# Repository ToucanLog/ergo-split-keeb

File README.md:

# ergo-split-keeb
rp2040 based split keyboard with trrs and usb-c (2.0). Using an ergodox-esque layout, but I wanted even more keys...

NOTE: The firmware is for use with QMK (https://github.com/qmk/qmk_firmware), however this keyboard does not have an official commit yet. Thus, simply copy this keyboard's firmware into a new sub-folder in the "keyboards" folder and flash from there. See the QMK CLI docs for flashing the keyboard for extra help. Please note that this firmware is exceptionally early stage, and while completely functional, is relatively bare-bones. 

`qmk flash -kb "/ENTER PATH HERE" -km default -bl uf2-split-left`

`qmk flash -kb "/ENTER PATH HERE" -km default -bl uf2-split-right`

See Schematic for 1 PCB (Left)

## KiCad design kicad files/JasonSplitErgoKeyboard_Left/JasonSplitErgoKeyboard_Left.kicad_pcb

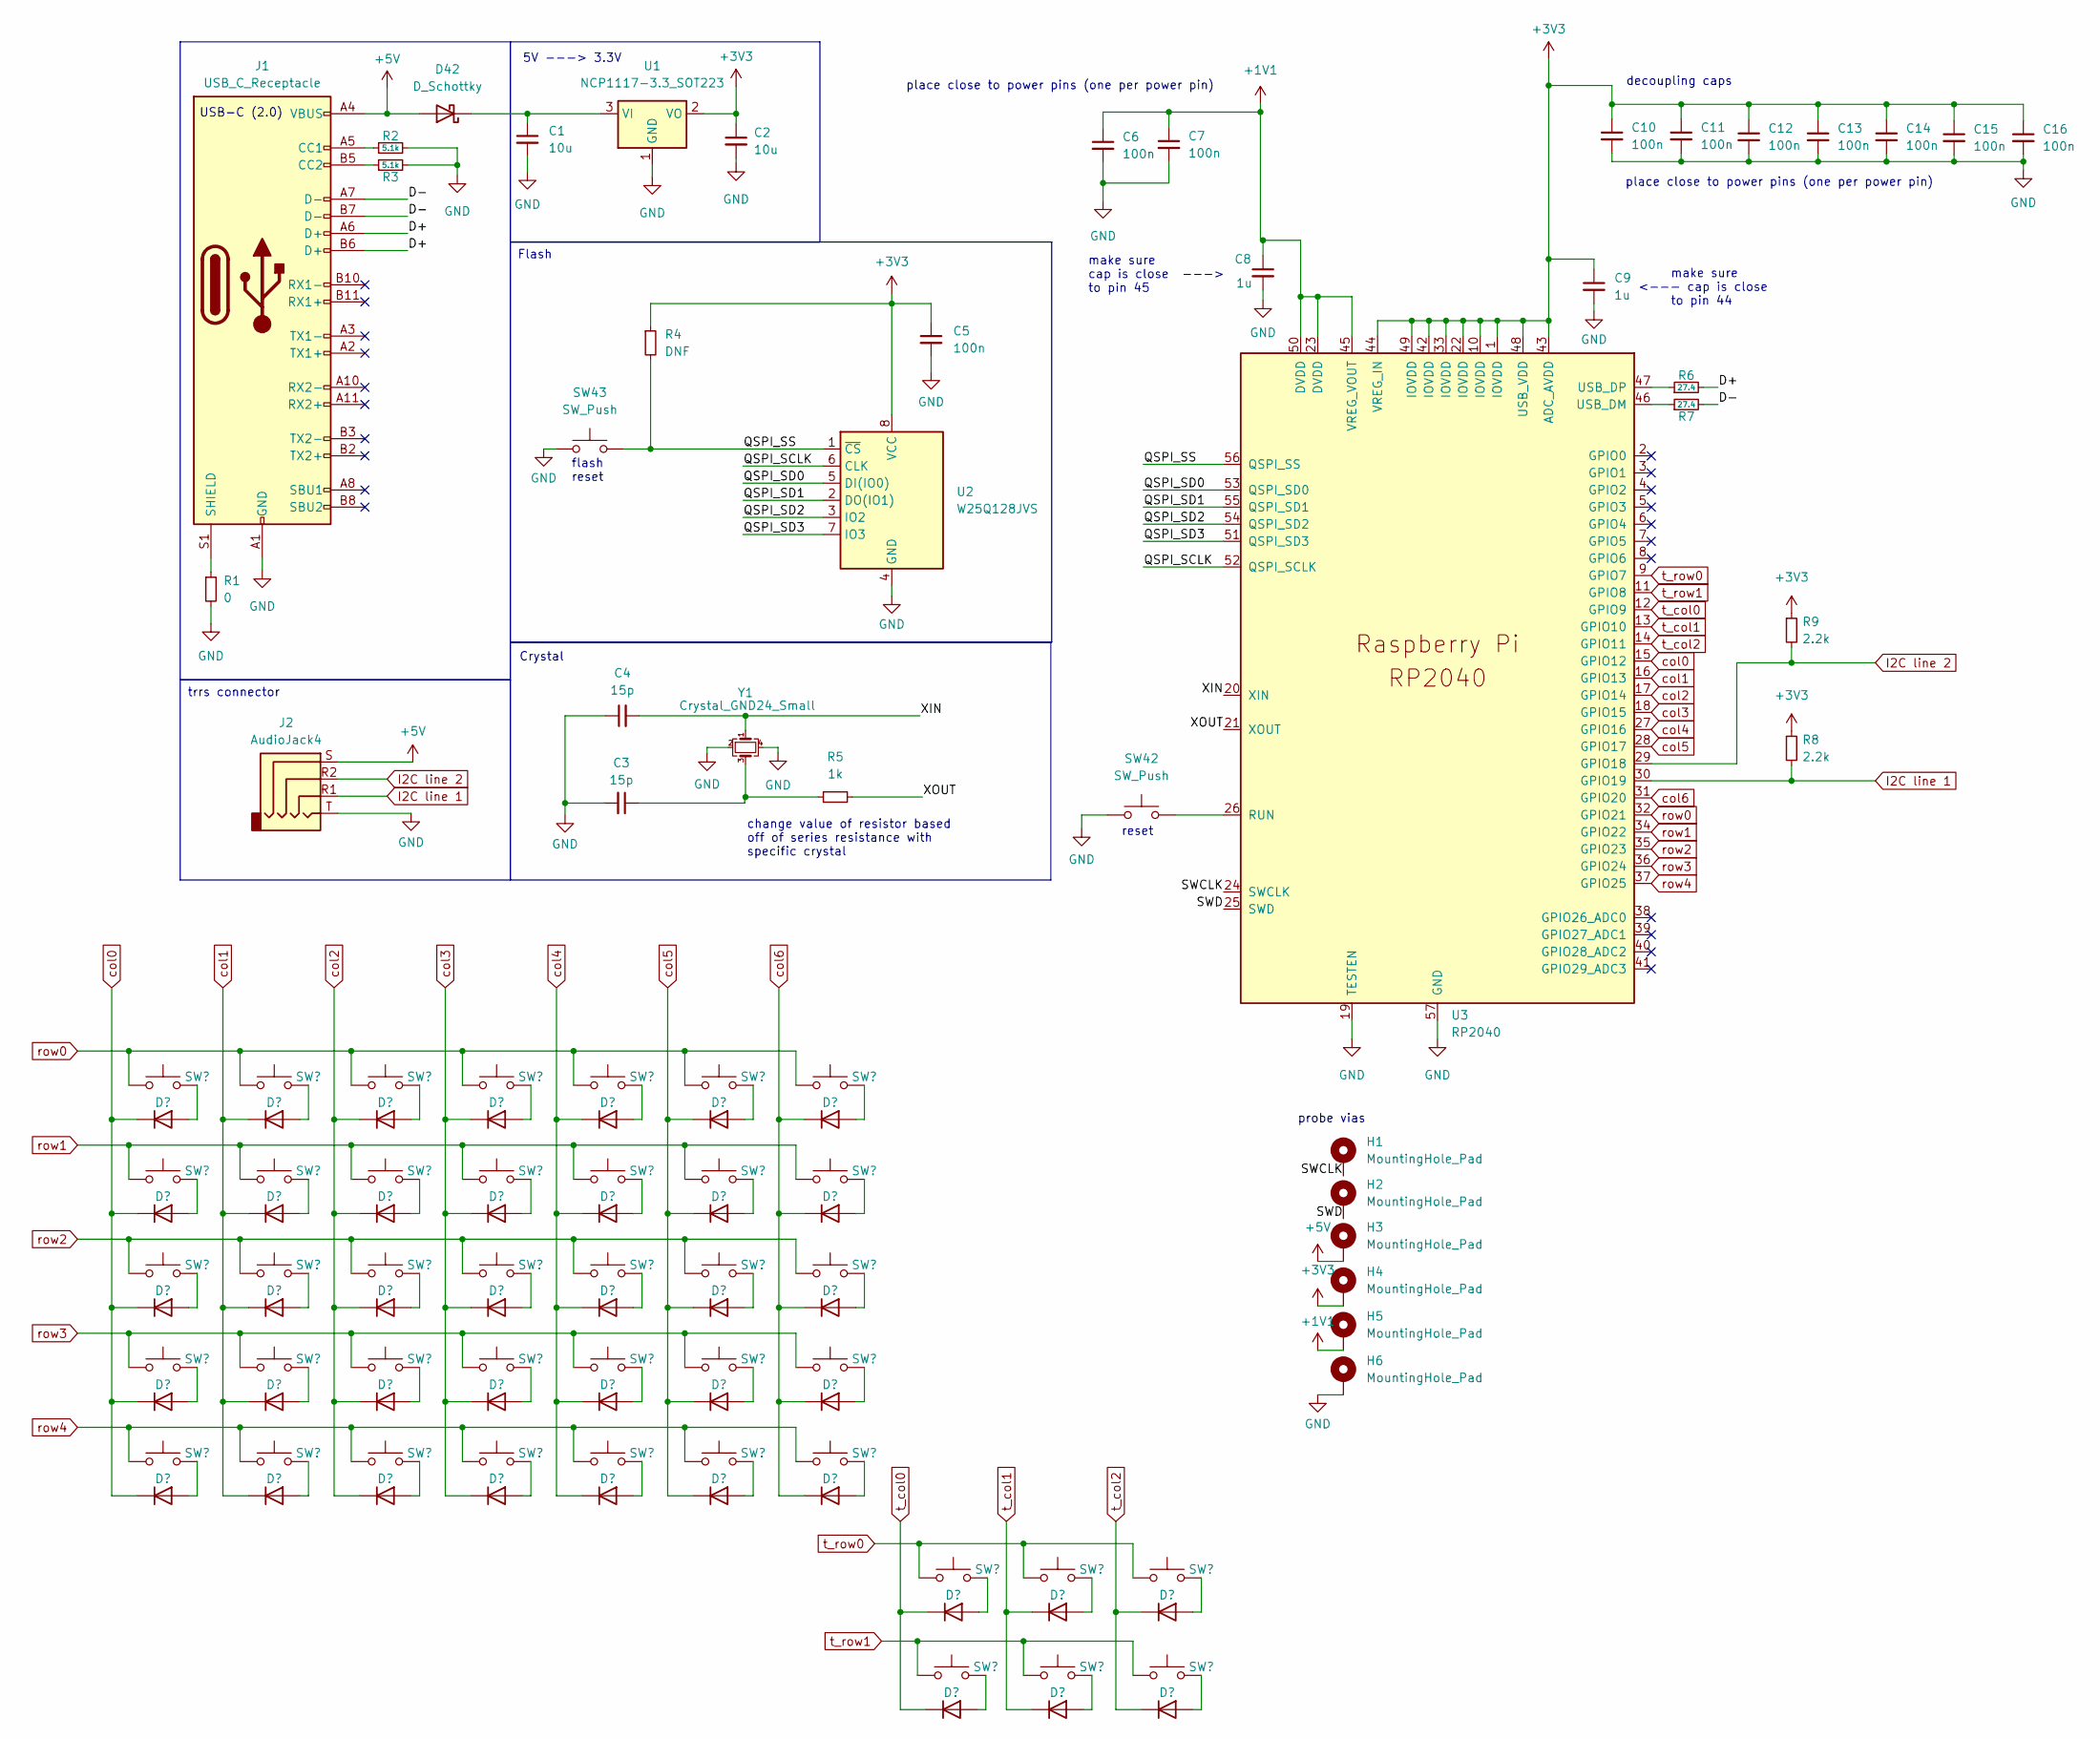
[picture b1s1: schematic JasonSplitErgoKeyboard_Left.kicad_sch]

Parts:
C1, C2: 10u; C_0603_1608Metric
C3, C4: 15p; C_0603_1608Metric
C5, C6, C7, C10, C11, C12, C13, C14, C15, C16: 100n; C_0603_1608Metric
C8, C9: 1u; C_0603_1608Metric
D1, D2, D3, D4, D5, D6, D7, D8, D9, D10, D11, D12, D13, D14, D15, D16, D17, D18, D19, D20, D21, D22, D23, D24, D25, D26, D27, D28, D29, D30, D31, D32, D33, D34, D35, D36, D37, D38, D39, D40, D41: D; D_SOD-323
D42: D_Schottky; D_SOD-323
H1, H2, H3, H4, H5, H6: MountingHole_Pad; MountingHole_2.2mm_M2_DIN965_Pad
J1: USB_C_Receptacle; USB_C_Receptacle_G-Switch_GT-USB-7010ASV
J2: AudioJack4; Jack_3.5mm_PJ320D_Horizontal
R1: 0; R_0603_1608Metric
R2, R3: 5.1k; R_0603_1608Metric
R4: DNF; R_0603_1608Metric
R5: 1k; R_0603_1608Metric
R6, R7: 27.4; R_0603_1608Metric
R8, R9: 2.2k; R_0603_1608Metric
SW1, SW2, SW3, SW4, SW7, SW8, SW9, SW10, SW11, SW12, SW13, SW14, SW15, SW16, SW17, SW18, SW19, SW20, SW21, SW22, SW23, SW24, SW25, SW26, SW27, SW28, SW29, SW30, SW31, SW32, SW33, SW34, SW35, SW36, SW41: SW_Push; SW_Cherry_MX_1.00u_PCB
SW5, SW6: SW_Push; SW_Cherry_MX_2.00u_PCB
SW37, SW38, SW39, SW40: SW_Push; SW_Cherry_MX_1.50u_PCB
SW42, SW43: SW_Push; 3.9×2.9mm Compact Type
U1: NCP1117-3.3_SOT223; SOT-223-3_TabPin2
U2: W25Q128JVS; SOIC-8_5.23x5.23mm_P1.27mm
U3: RP2040; QFN-56-1EP_7x7mm_P0.4mm_EP4x4mm
Y1: Crystal_GND24_Small; Crystal_SMD_3225-4Pin_3.2x2.5mm

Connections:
+1V1: C6.1, C7.1, C8.1, H5.1, U3.23 (DVDD), U3.45 (VREG_VOUT), U3.50 (DVDD)
+3V3: C2.1, C5.1, C9.1, C10.1, C11.1, C12.1, C13.1, C14.1, C15.1, C16.1, H4.1, R4.1, R8.1, R9.1, U1.2 (VO), U2.8 (VCC), U3.1 (IOVDD), U3.10 (IOVDD), U3.22 (IOVDD), U3.33 (IOVDD), U3.42 (IOVDD), U3.43 (ADC_AVDD), U3.44 (VREG_IN), U3.48 (USB_VDD), U3.49 (IOVDD)
+5V: D42.2 (A), H3.1, J1.A4 (VBUS), J1.A9 (VBUS), J1.B4 (VBUS), J1.B9 (VBUS), J2.S
/D+: J1.A6 (D+), J1.B6 (D+), R6.2
/D-: J1.A7 (D-), J1.B7 (D-), R7.2
/QSPI_SCLK: U2.6 (CLK), U3.52 (QSPI_SCLK)
/QSPI_SD0: U2.5 (DI(IO0)), U3.53 (QSPI_SD0)
/QSPI_SD1: U2.2 (DO(IO1)), U3.55 (QSPI_SD1)
/QSPI_SD2: U2.3 (IO2), U3.54 (QSPI_SD2)
/QSPI_SD3: U2.7 (IO3), U3.51 (QSPI_SD3)
/QSPI_SS: R4.2, SW43.2, U2.1 (~CS), U3.56 (QSPI_SS)
/SWCLK: H1.1, U3.24 (SWCLK)
/SWD: H2.1, U3.25 (SWD)
/XIN: C4.2, U3.20 (XIN), Y1.1
/XOUT: R5.2, U3.21 (XOUT)
GND: C1.2, C2.2, C3.2, C4.1, C5.2, C6.2, C7.2, C8.2, C9.2, C10.2, C11.2, C12.2, C13.2, C14.2, C15.2, C16.2, H6.1, J1.A1 (GND), J1.A12 (GND), J1.B1 (GND), J1.B12 (GND), J2.T, R1.2, R2.2, R3.2, SW42.1, SW43.1, U1.1 (GND), U2.4 (GND), U3.19 (TESTEN), U3.57 (GND), Y1.2, Y1.4
I2C line 1: J2.R1, R8.2, U3.30 (GPIO19)
I2C line 2: J2.R2, R9.2, U3.29 (GPIO18)
unnamed: C3.1, R5.1, Y1.3
unnamed: D1.2 (A), SW1.2
unnamed: D2.2 (A), SW2.2
unnamed: D3.2 (A), SW3.2
unnamed: D4.2 (A), SW4.2
unnamed: D5.2 (A), SW5.2
unnamed: D6.2 (A), SW6.2
unnamed: D7.2 (A), SW7.2
unnamed: D8.2 (A), SW8.2
unnamed: D9.2 (A), SW9.2
unnamed: D10.2 (A), SW10.2
unnamed: D11.2 (A), SW11.2
unnamed: D12.2 (A), SW12.2
unnamed: D13.2 (A), SW13.2
unnamed: D14.2 (A), SW14.2
unnamed: D15.2 (A), SW15.2
unnamed: D16.2 (A), SW16.2
unnamed: D17.2 (A), SW17.2
unnamed: D18.2 (A), SW18.2
unnamed: D19.2 (A), SW19.2
unnamed: D20.2 (A), SW20.2
unnamed: D21.2 (A), SW21.2
unnamed: D22.2 (A), SW22.2
unnamed: D23.2 (A), SW23.2
unnamed: D24.2 (A), SW24.2
unnamed: D25.2 (A), SW25.2
unnamed: D26.2 (A), SW26.2
unnamed: D27.2 (A), SW27.2
unnamed: D28.2 (A), SW28.2
unnamed: D29.2 (A), SW29.2
unnamed: D30.2 (A), SW30.2
unnamed: D31.2 (A), SW31.2
unnamed: D32.2 (A), SW32.2
unnamed: D33.2 (A), SW33.2
unnamed: D34.2 (A), SW34.2
unnamed: D35.2 (A), SW35.2
unnamed: D36.2 (A), SW36.2
unnamed: D37.2 (A), SW37.2
unnamed: D38.2 (A), SW38.2
unnamed: D39.2 (A), SW39.2
unnamed: D40.2 (A), SW40.2
unnamed: D41.2 (A), SW41.2
unnamed: C1.1, D42.1 (K), U1.3 (VI)
unnamed: J1.A5 (CC1), R2.1
unnamed: J1.B5 (CC2), R3.1
unnamed: J1.S1 (SHIELD), R1.1
unnamed: SW42.2, U3.26 (RUN)
unnamed: R7.1, U3.46 (USB_DM)
unnamed: R6.1, U3.47 (USB_DP)
col0: D7.1 (K), D8.1 (K), D9.1 (K), D10.1 (K), D11.1 (K), U3.15 (GPIO12)
col1: D12.1 (K), D13.1 (K), D14.1 (K), D15.1 (K), D16.1 (K), U3.16 (GPIO13)
col2: D17.1 (K), D18.1 (K), D19.1 (K), D20.1 (K), D21.1 (K), U3.17 (GPIO14)
col3: D22.1 (K), D23.1 (K), D24.1 (K), D25.1 (K), D26.1 (K), U3.18 (GPIO15)
col4: D27.1 (K), D28.1 (K), D29.1 (K), D30.1 (K), D31.1 (K), U3.27 (GPIO16)
col5: D32.1 (K), D33.1 (K), D34.1 (K), D35.1 (K), D36.1 (K), U3.28 (GPIO17)
col6: D37.1 (K), D38.1 (K), D39.1 (K), D40.1 (K), D41.1 (K), U3.31 (GPIO20)
row0: SW7.1, SW12.1, SW17.1, SW22.1, SW27.1, SW32.1, SW37.1, U3.32 (GPIO21)
row1: SW8.1, SW13.1, SW18.1, SW23.1, SW28.1, SW33.1, SW38.1, U3.34 (GPIO22)
row2: SW9.1, SW14.1, SW19.1, SW24.1, SW29.1, SW34.1, SW39.1, U3.35 (GPIO23)
row3: SW10.1, SW15.1, SW20.1, SW25.1, SW30.1, SW35.1, SW40.1, U3.36 (GPIO24)
row4: SW11.1, SW16.1, SW21.1, SW26.1, SW31.1, SW36.1, SW41.1, U3.37 (GPIO25)
t_col0: D1.1 (K), D6.1 (K), U3.12 (GPIO9)
t_col1: D2.1 (K), D5.1 (K), U3.13 (GPIO10)
t_col2: D3.1 (K), D4.1 (K), U3.14 (GPIO11)
t_row0: SW1.1, SW2.1, SW3.1, U3.9 (GPIO7)
t_row1: SW4.1, SW5.1, SW6.1, U3.11 (GPIO8)

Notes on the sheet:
trrs connector
Flash
reset
make sure <--- cap is close to pin 44
flash reset
probe vias
place close to power pins (one per power pin)
5V ---> 3.3V
change value of resistor based off of series resistance with specific crystal
make sure cap is close ---> to pin 45
Crystal
decoupling caps
USB-C (2.0)

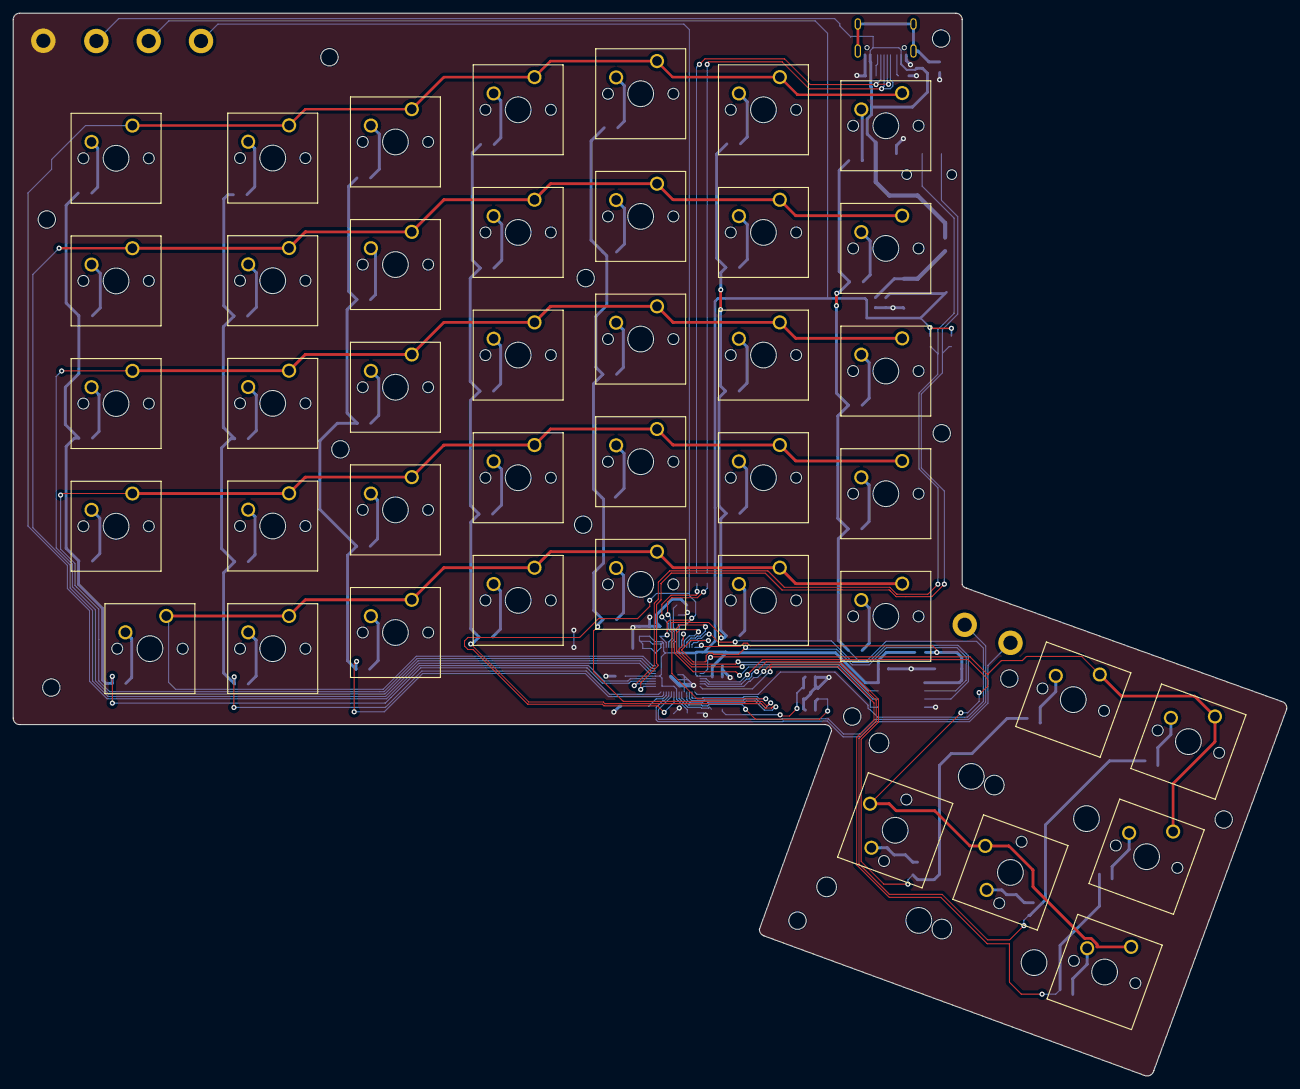
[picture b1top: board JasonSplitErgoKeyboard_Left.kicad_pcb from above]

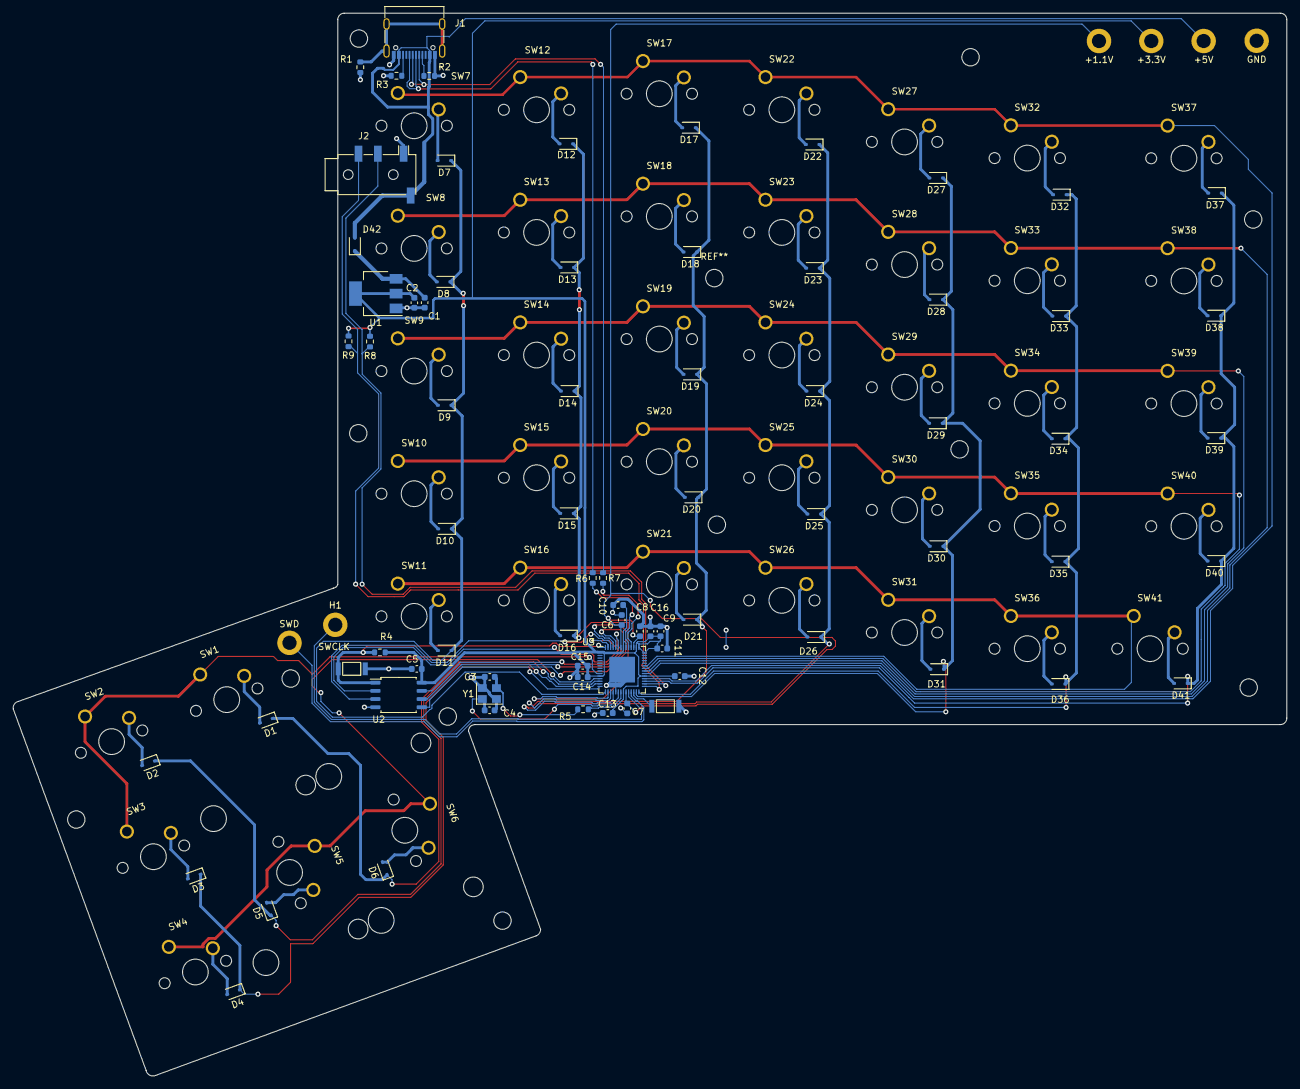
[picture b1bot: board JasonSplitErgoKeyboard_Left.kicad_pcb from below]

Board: 2 copper layers, 197.8 x 165.1 mm, 122 parts (81 on the bottom side), 84 nets.

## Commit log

2025-01-24 adding firmware files (qmk)
2025-01-26 adding pcb files, including both kicad and prodcution gerber
2025-01-27 adding enclosure files
